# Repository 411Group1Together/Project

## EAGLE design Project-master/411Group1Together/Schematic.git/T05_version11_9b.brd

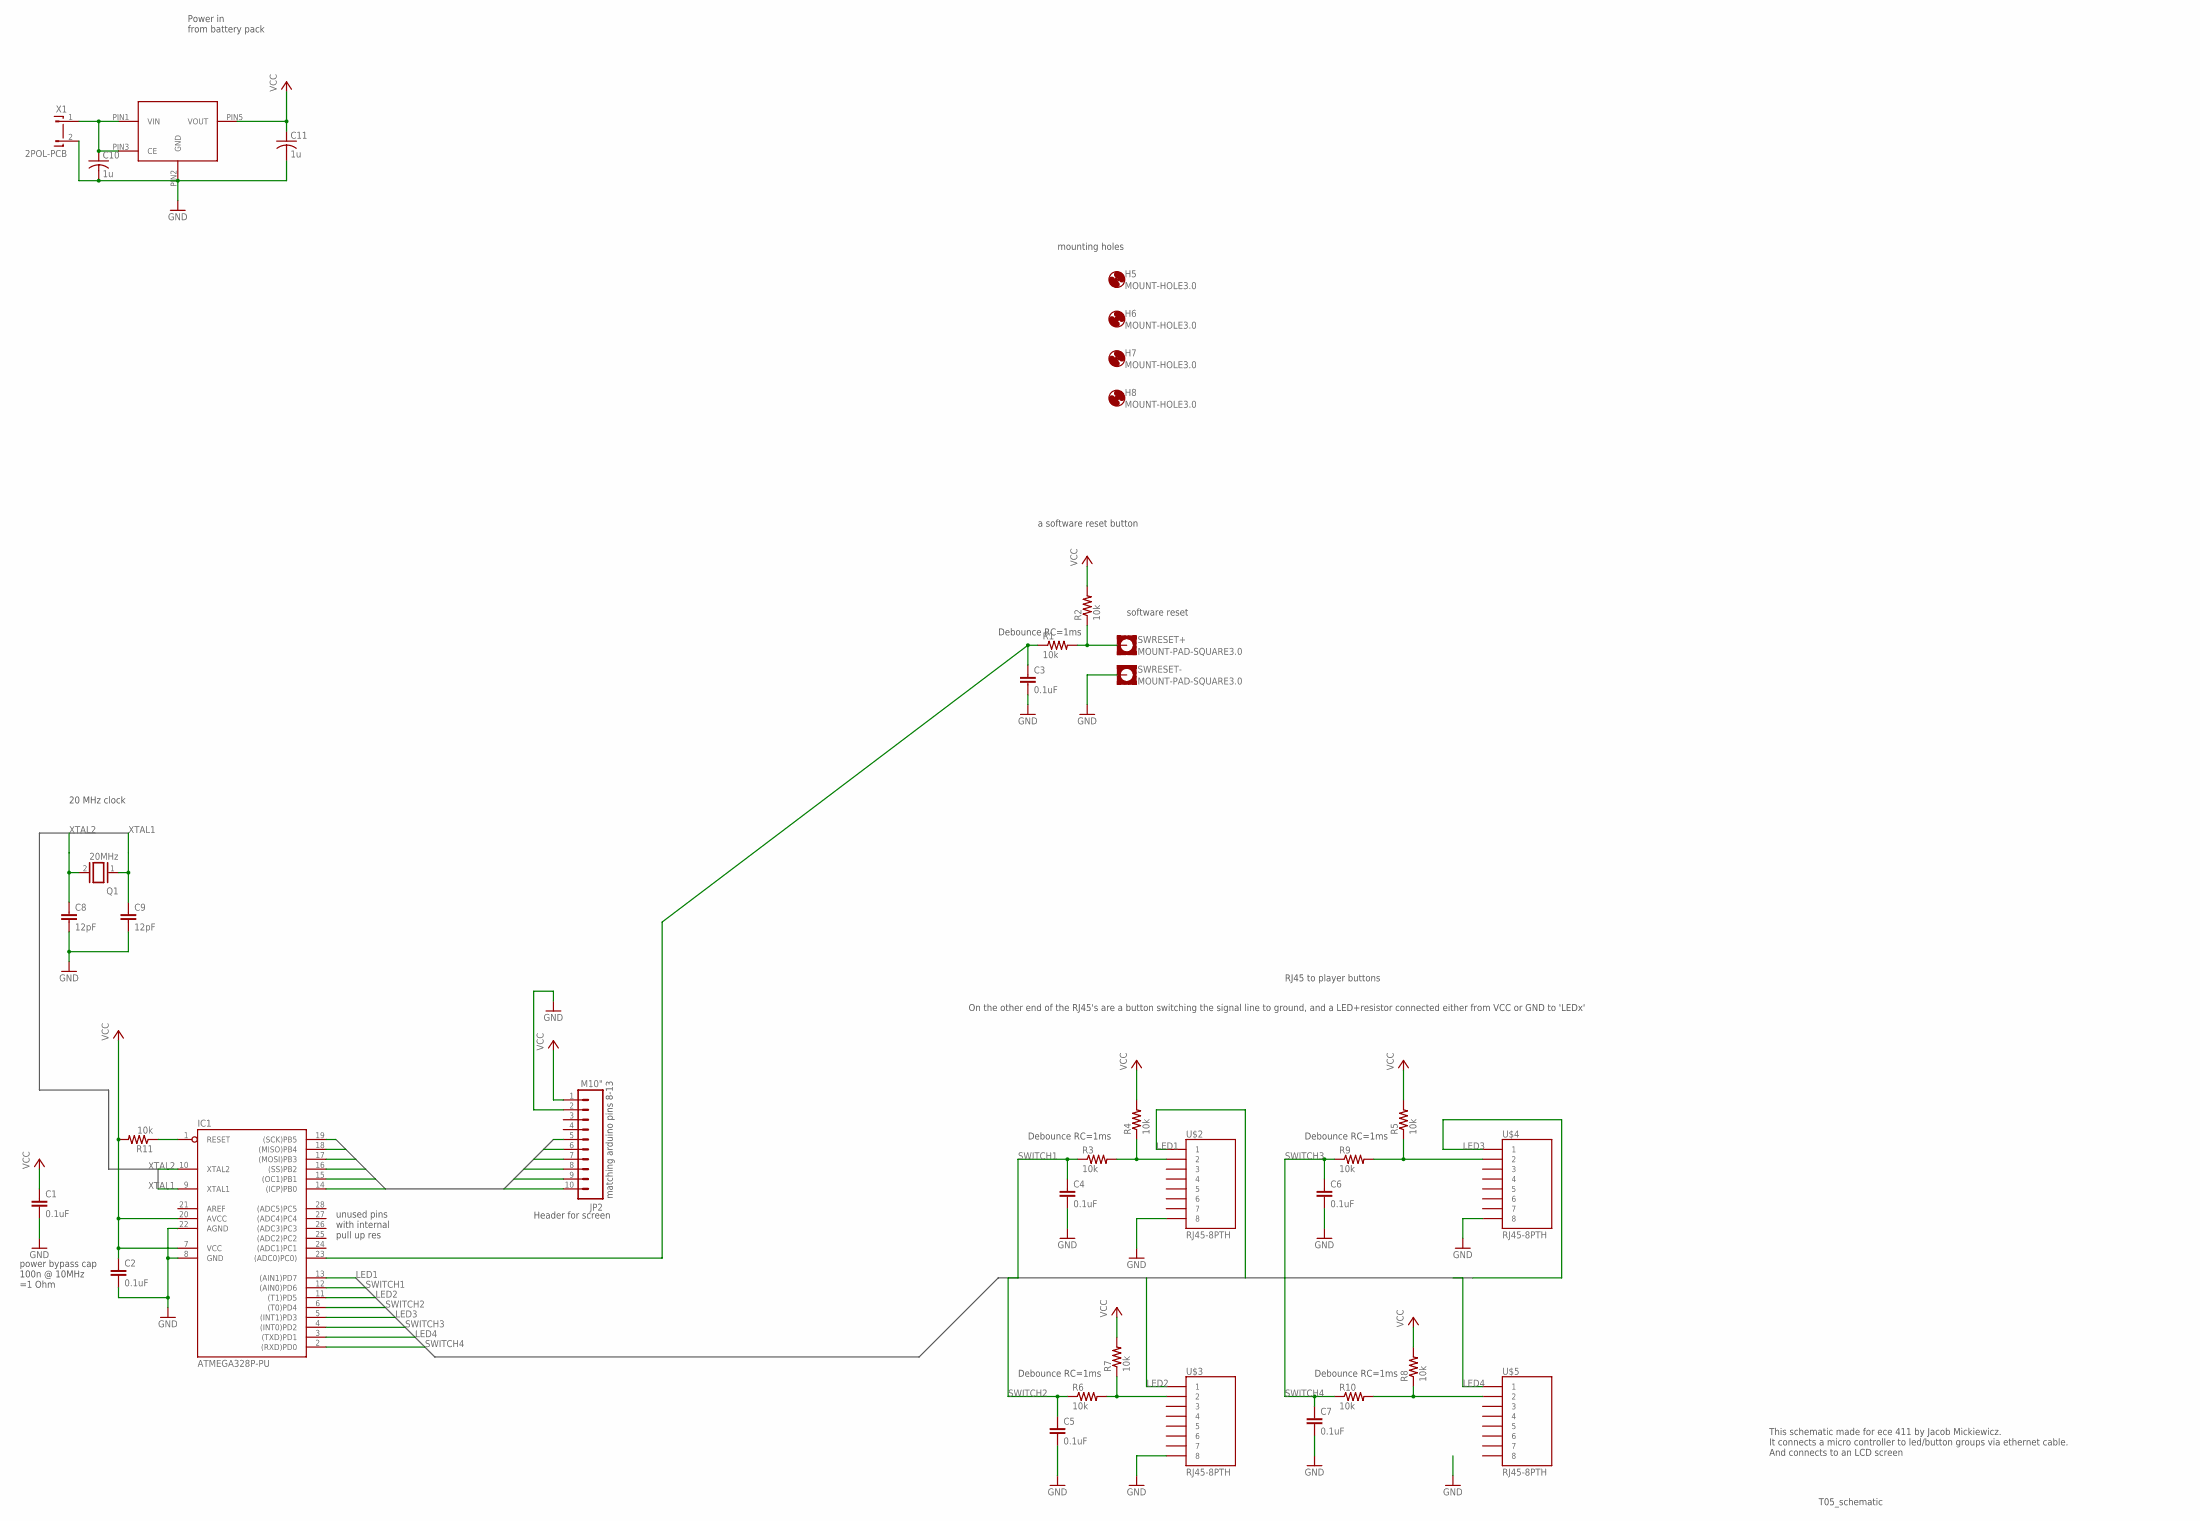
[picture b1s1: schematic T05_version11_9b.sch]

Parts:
C1, C2, C3, C4, C5, C6, C7: 0.1uF; 0603-CAP
C8, C9: 12pF; 0603-CAP
C10, C11: 1u; C0603
H5, H6, H7, H8: MOUNT-HOLE3.0; 3,0
IC1: ATMEGA328P-PU; DIL28-3
JP2: M10"; 1X10
Q1: 20MHz; QS
R1, R2, R3, R4, R5, R6, R7, R8, R9, R10, R11: 10k; 0603-RES
SWRESET+: MOUNT-PAD-SQUARE3.0; 3,0-PAD-SQUARE
SWRESET-: MOUNT-PAD-SQUARE3.0; 3,0-PAD-SQUARE
U$1: NCP4625
U$2, U$3, U$4, U$5: RJ45-8PTH; RJ45-8
X1: 2POL-PCB

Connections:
GND: C1.2, C2.2, C3.2, C4.2, C5.2, C6.2, C7.2, C8.2, C9.2, C10.2, C11.2, IC1.8 (GND), IC1.22 (AGND), JP2.2, SWRESET-.B3,0, U$1.PIN2 (GND), U$2.8, U$3.8, U$4.8, X1.2
ICP: IC1.14 ((ICP)PB0), JP2.10
LED1: IC1.13 ((AIN1)PD7), U$2.1
LED2: IC1.11 ((T1)PD5), U$3.1
LED3: IC1.5 ((INT1)PD3), U$4.1
LED4: IC1.3 ((TXD)PD1), U$5.1
MISO: IC1.18 ((MISO)PB4), JP2.6
MOSI: IC1.17 ((MOSI)PB3), JP2.7
unnamed: IC1.1 (RESET), R11.1
unnamed: R3.2, R4.1, U$2.2
unnamed: R8.1, R10.2, U$5.2
unnamed: R1.2, R2.1, SWRESET+.B3,0
unnamed: R6.2, R7.1, U$3.2
unnamed: R5.1, R9.2, U$4.2
unnamed: C10.1, U$1.PIN1 (VIN), U$1.PIN3 (CE), X1.1
OC1: IC1.15 ((OC1)PB1), JP2.9
SCK: IC1.19 ((SCK)PB5), JP2.5
SS: IC1.16 ((SS)PB2), JP2.8
SWITCH1: C4.1, IC1.12 ((AIN0)PD6), R3.1
SWITCH2: C5.1, IC1.6 ((T0)PD4), R6.1
SWITCH3: C6.1, IC1.4 ((INT0)PD2), R9.1
SWITCH4: C7.1, IC1.2 ((RXD)PD0), R10.1
SW_RESET: C3.1, IC1.23 ((ADC0)PC0)), R1.1
VCC: C1.1, C2.1, C11.1, IC1.7 (VCC), IC1.20 (AVCC), JP2.1, R2.2, R4.2, R5.2, R7.2, R8.2, R11.2, U$1.PIN5 (VOUT)
XTAL1: C9.1, IC1.9 (XTAL1), Q1.1
XTAL2: C8.1, IC1.10 (XTAL2), Q1.2

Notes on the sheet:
power bypass cap 100n @ 10MHz =1 Ohm
Header for screen
Debounce RC=1ms
software reset
RJ45 to player buttons
unused pins with internal pull up res
T05_schematic
matching arduino pins 8-13
This schematic made for ece 411 by Jacob Mickiewicz. It connects a micro controller to led/button groups via ethernet cable. And connects to an LCD screen
On the other end of the RJ45's are a button switching the signal line to ground, and a LED+resistor connected either from VCC or GND to 'LEDx'
Power in from battery pack
a software reset button
mounting holes
20 MHz clock

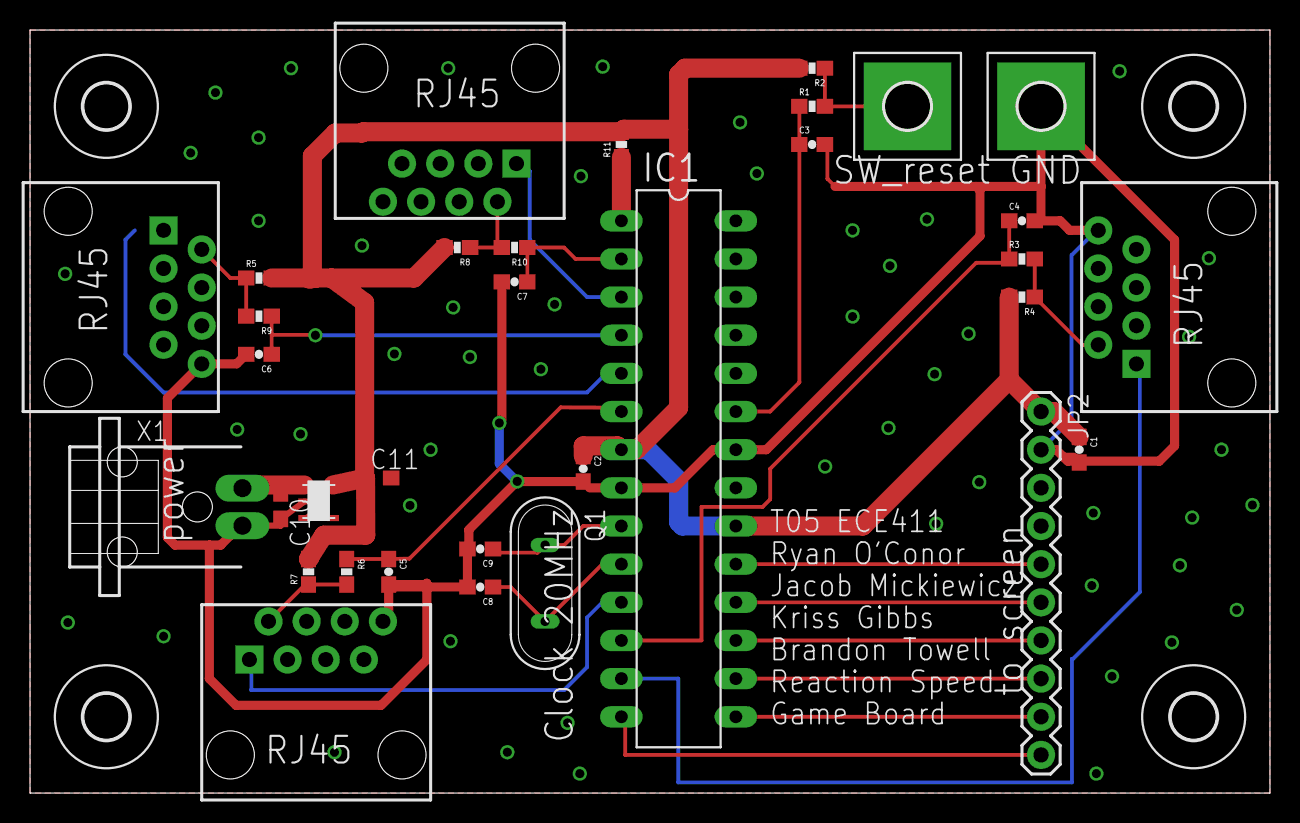
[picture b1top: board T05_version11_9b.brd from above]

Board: 2 copper layers, 82.5 x 50.8 mm, 37 parts (0 on the bottom side), 26 nets.

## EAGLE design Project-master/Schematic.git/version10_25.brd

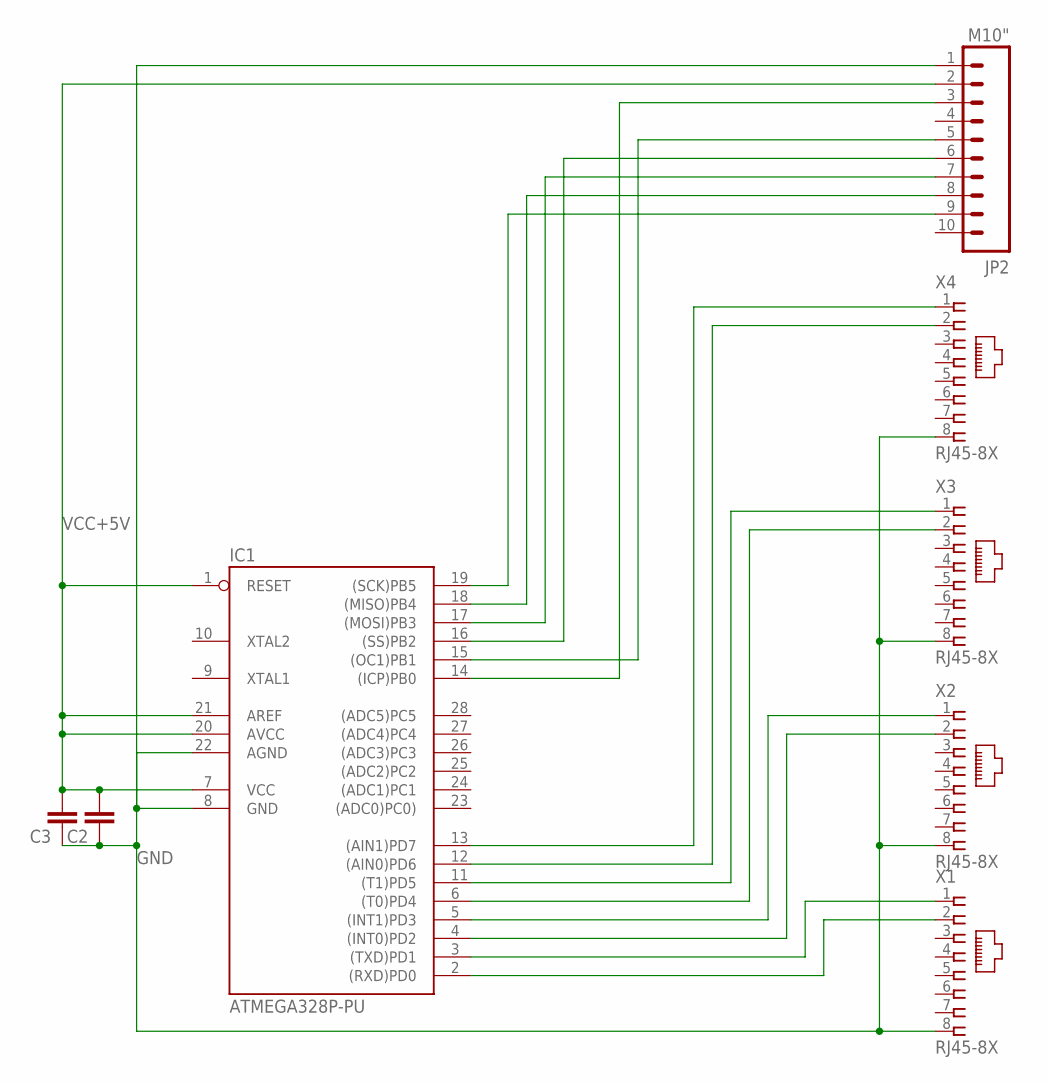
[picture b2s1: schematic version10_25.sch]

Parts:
C2, C3: CAP1206; 1206
IC1: ATMEGA328P-PU; DIL28-3
JP2: M10"; 1X10
X1, X2, X3, X4: RJ45-8X; RJ45-NO-SHIELD

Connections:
GND: C2.1, C3.1, IC1.8 (GND), IC1.22 (AGND), JP2.1, X1.8, X2.8, X3.8, X4.8
unnamed: IC1.19 ((SCK)PB5), JP2.9
unnamed: IC1.18 ((MISO)PB4), JP2.8
unnamed: IC1.15 ((OC1)PB1), JP2.5
unnamed: IC1.17 ((MOSI)PB3), JP2.7
unnamed: IC1.16 ((SS)PB2), JP2.6
unnamed: IC1.14 ((ICP)PB0), JP2.3
unnamed: IC1.2 ((RXD)PD0), X1.2
unnamed: IC1.3 ((TXD)PD1), X1.1
unnamed: IC1.4 ((INT0)PD2), X2.2
unnamed: IC1.5 ((INT1)PD3), X2.1
unnamed: IC1.6 ((T0)PD4), X3.2
unnamed: IC1.11 ((T1)PD5), X3.1
unnamed: IC1.12 ((AIN0)PD6), X4.2
unnamed: IC1.13 ((AIN1)PD7), X4.1
VCC+5V: C2.2, C3.2, IC1.1 (RESET), IC1.7 (VCC), IC1.20 (AVCC), IC1.21 (AREF), JP2.2

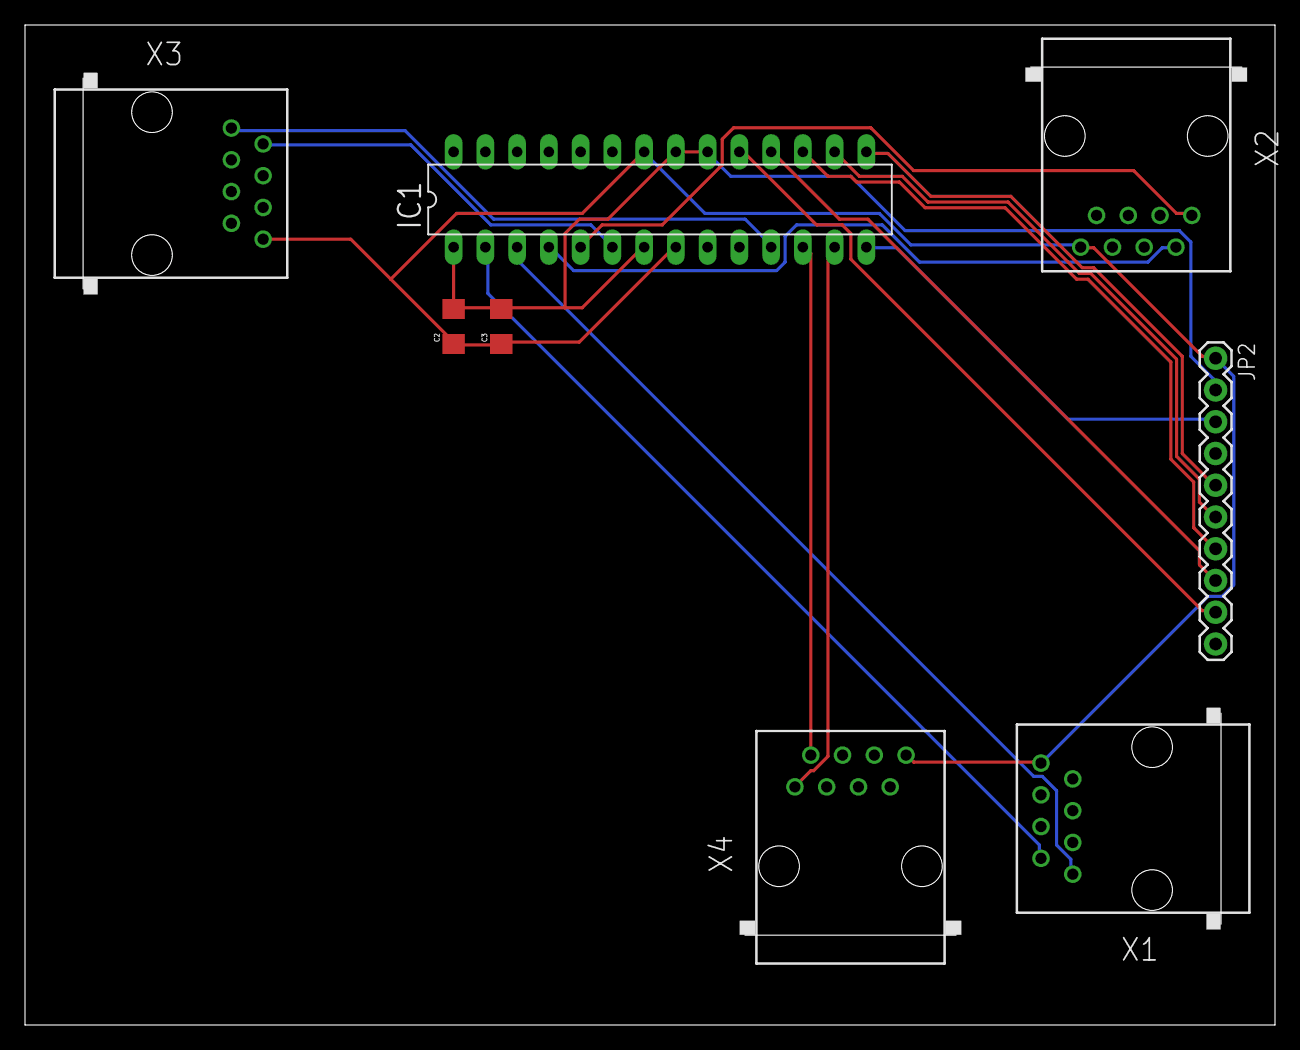
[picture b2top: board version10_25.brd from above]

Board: 2 copper layers, 100.0 x 80.0 mm, 8 parts (0 on the bottom side), 16 nets.

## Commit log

2014-11-10 updated power, gnd.
2014-11-10 ran drc/erc. fixed a clearence and some naming.
2014-11-17 added block diagram
2014-12-03 test plan
2014-12-12 checked in arduino code
2014-12-12 fixed winner evaluation case
2014-12-12 fixed the display of the winner
    added a winners time in milliseconds
2014-12-12 fixed winner declaration
    there was a bug that if someone didn’t push their button they would be
    declared the winner
2014-12-12 cleaned up the display code
2014-12-12 upload the display functions tab
2014-12-12 bom breakdown
2014-12-12 final code upload.
    changed the way the button press is captured

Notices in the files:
parts and their libraries:
SparkFun-Capacitors: Licensing: Creative Commons ShareAlike 4.0 International - https://creativecommons.org/licenses/by-sa/4.0
